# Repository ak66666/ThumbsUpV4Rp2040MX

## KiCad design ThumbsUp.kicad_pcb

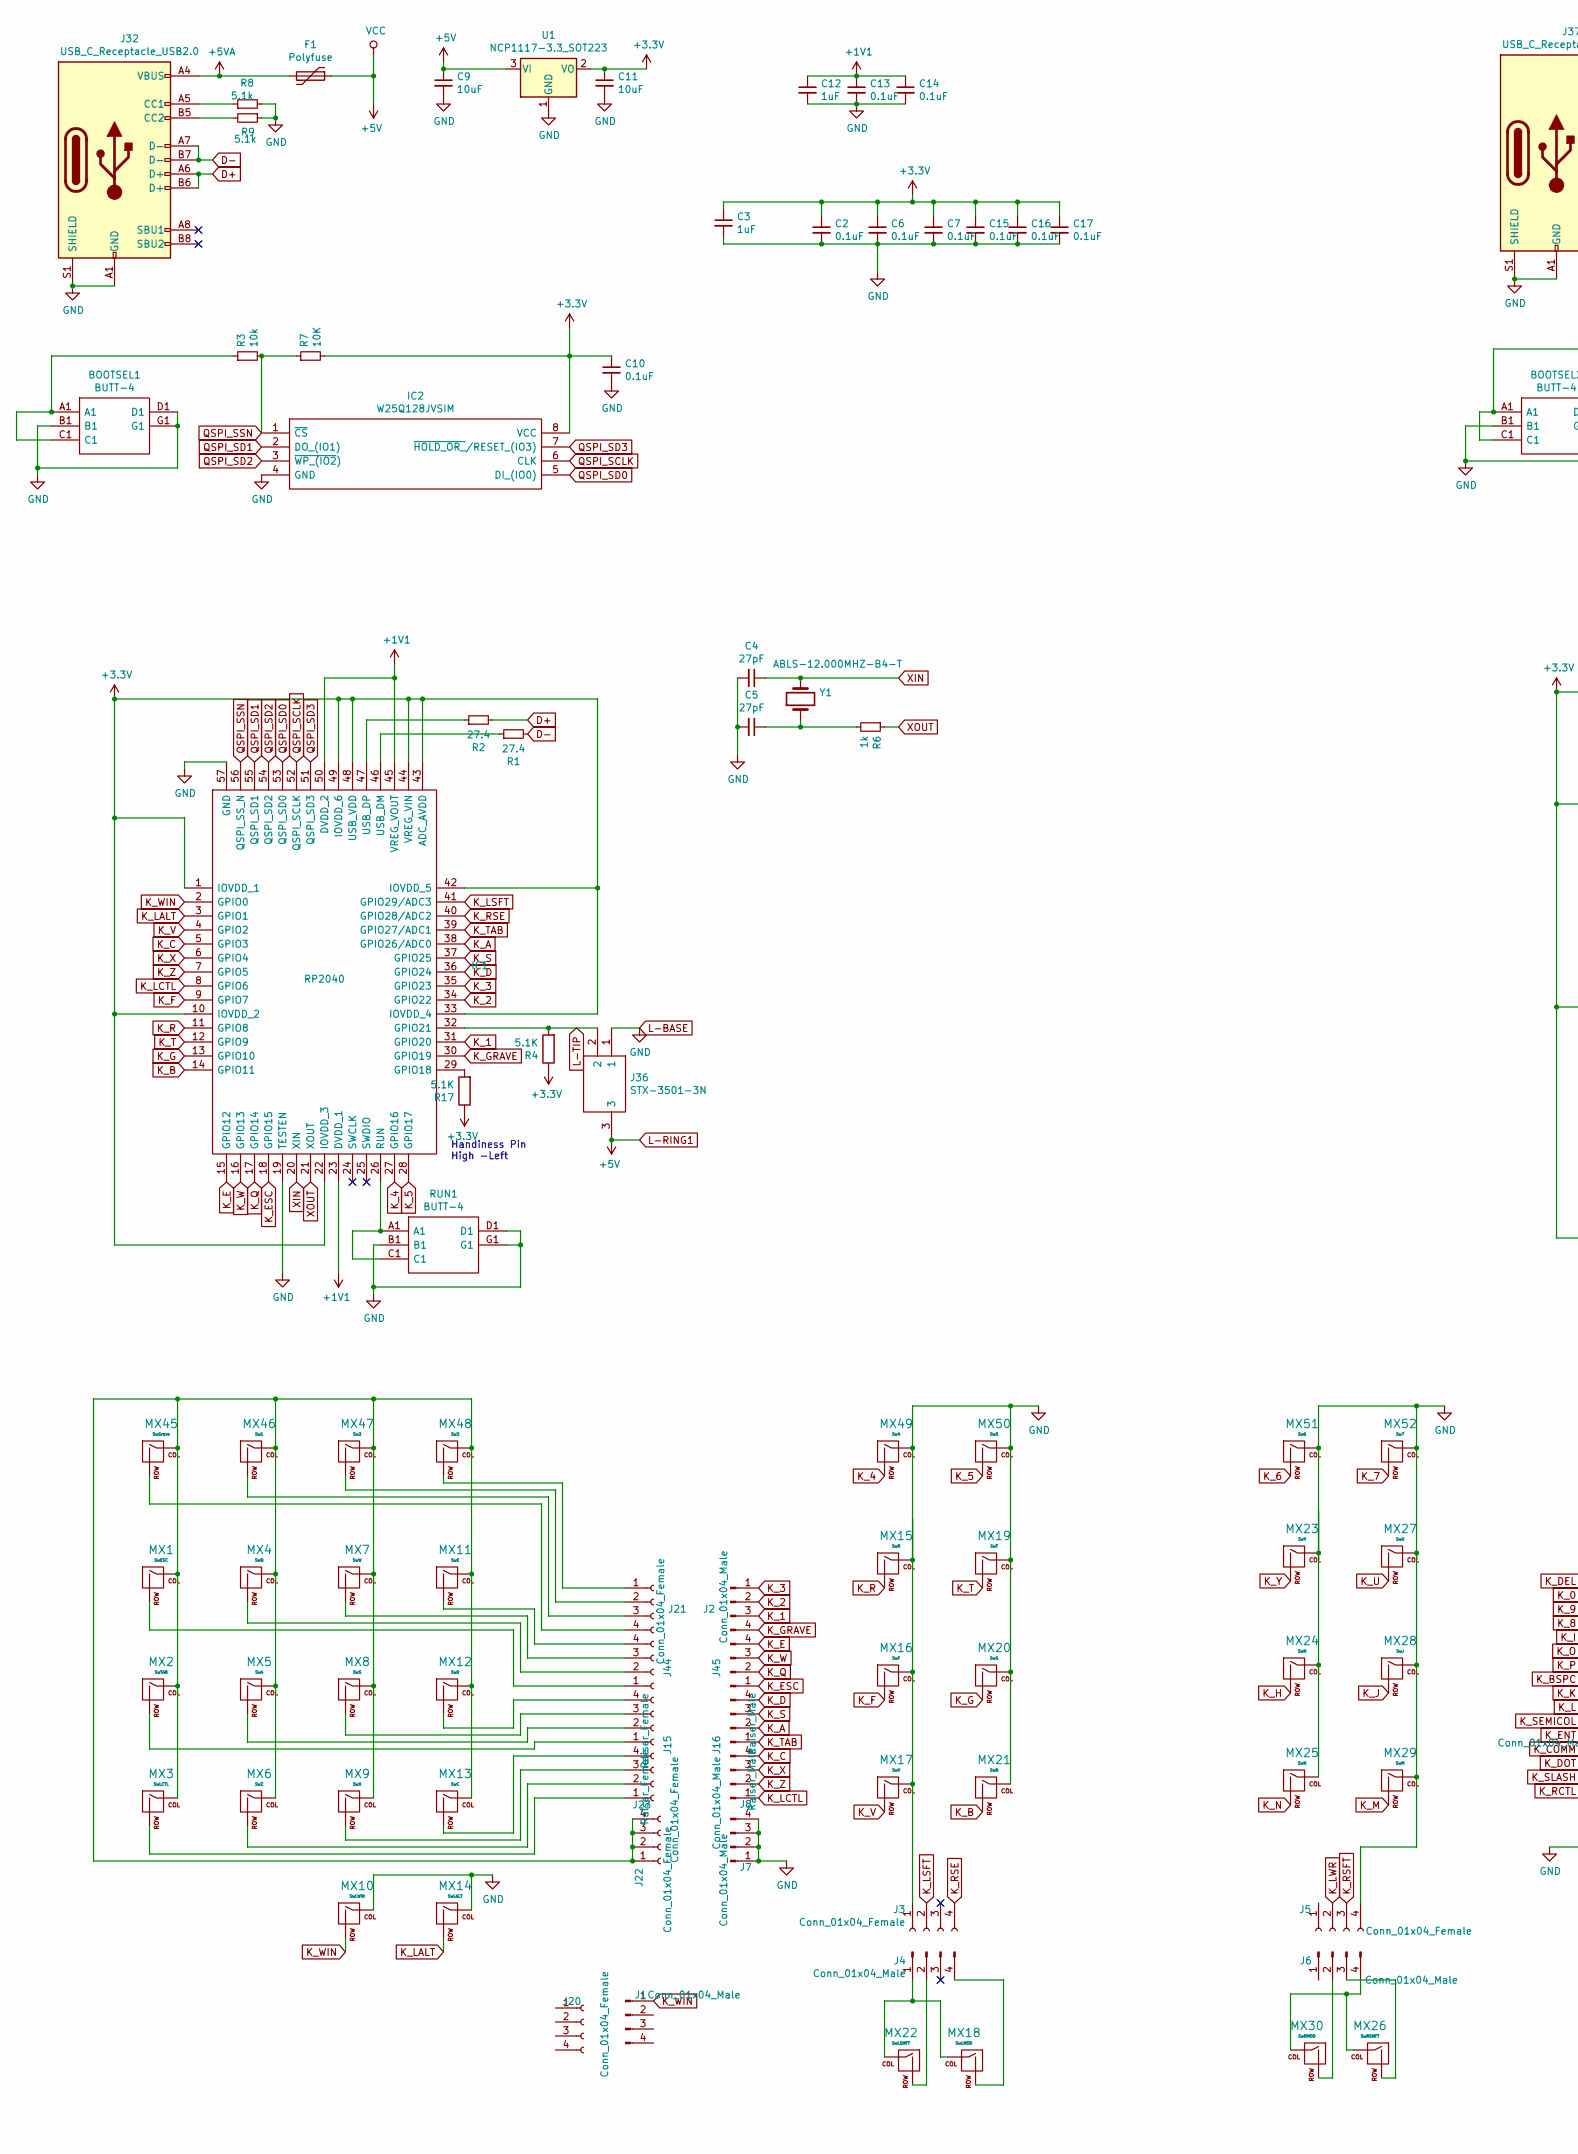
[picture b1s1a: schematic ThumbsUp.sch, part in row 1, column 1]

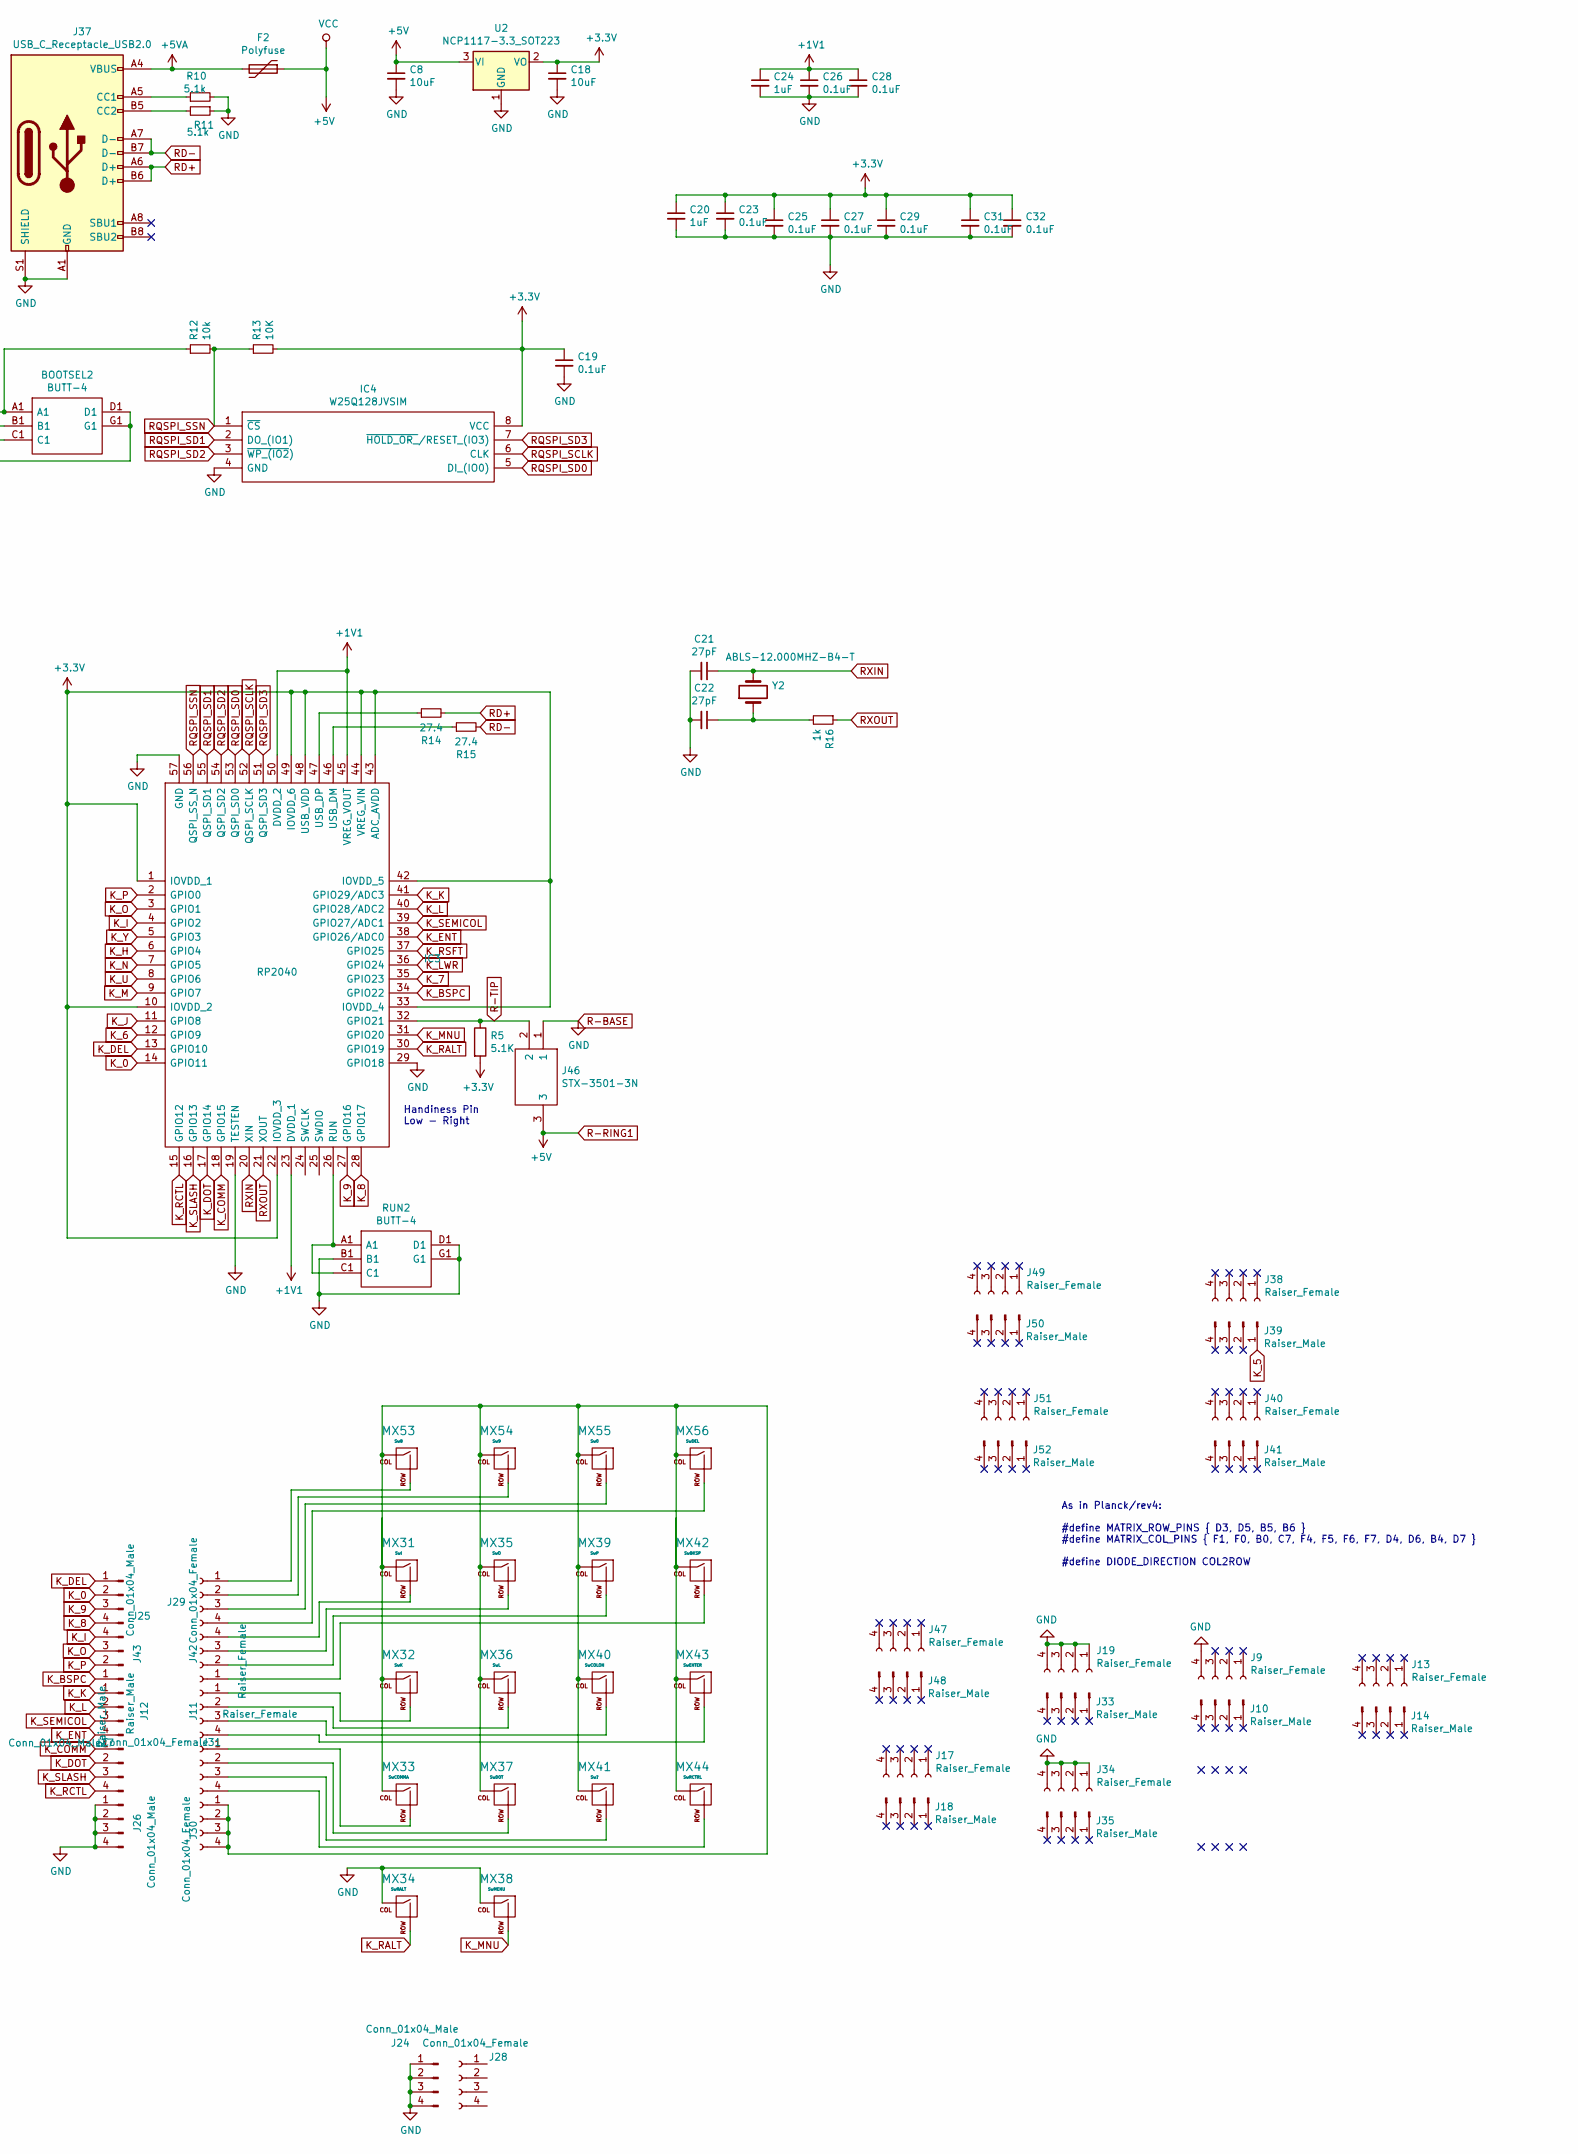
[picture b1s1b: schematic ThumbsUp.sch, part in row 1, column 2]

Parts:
BOOTSEL1, BOOTSEL2: BUTT-4; BUTT4; Manufacturer_Part_Number BUTT-4; Mouser Part Number 992-BUTT-4
C2, C6, C7, C10, C13, C14, C15, C16, C17, C19, C23, C25, C26, C27, C28, C29, C31, C32: 0.1uF; C_0402_1005Metric
C3, C12, C20, C24: 1uF; C_0402_1005Metric
C4, C5, C21, C22: 27pF; C_0402_1005Metric
C8, C9, C11, C18: 10uF; C_0402_1005Metric
F1, F2: Polyfuse; Fuse_1206_3216Metric
IC1, IC3: RP2040; QFN40P700X700X90-57N-D; Manufacturer_Part_Number RP2040
IC2, IC4: W25Q128JVSIM; SOIC127P790X216-8N; Manufacturer_Part_Number W25Q128JVSIM; Mouser Part Number 454-W25Q128JVSIM
J1, J2, J4, J6, J7, J8, J24, J25, J26, J27: Conn_01x04_Male; PinHeader_1x04_P2.54mm_Vertical
J3, J5, J20, J21, J22, J23, J28, J29, J30, J31: Conn_01x04_Female; PinSocket_1x04_P2.54mm_Vertical
J9, J11, J13, J15, J17, J19, J34, J38, J40, J42, J44, J47, J49, J51: Raiser_Female; PinSocket_1x04_P2.54mm_Vertical
J10, J12, J14, J16, J18, J33, J35, J39, J41, J43, J45, J48, J50, J52: Raiser_Male; PinHeader_1x04_P2.54mm_Vertical
J32, J37: USB_C_Receptacle_USB2.0; USB_C_Receptacle_Palconn_UTC16-G
J36, J46: STX-3501-3N; STX35013N; Manufacturer_Part_Number STX-3501-3N; Mouser Part Number 806-STX-3501-3N
MX1: SwESC; MX-1U-NoLED_HotSwap
MX2: SwTAB; MX-1U-NoLED_HotSwap
MX3: SwLCTL; MX-1U-NoLED_HotSwap
MX4: SwQ; MX-1U-NoLED_HotSwap
MX5: SwA; MX-1U-NoLED_HotSwap
MX6: SwZ; MX-1U-NoLED_HotSwap
MX7: SwW; MX-1U-NoLED_HotSwap
MX8: SwS; MX-1U-NoLED_HotSwap
MX9: SwX; MX-1U-NoLED_HotSwap
MX10: SwLWIN; MX-1U-NoLED_HotSwap
MX11: SwE; MX-1U-NoLED_HotSwap
MX12: SwD; MX-1U-NoLED_HotSwap
MX13: SwC; MX-1U-NoLED_HotSwap
MX14: SwLALT; MX-1U-NoLED_HotSwap
MX15: SwR; MX-1U-NoLED_HotSwap
MX16: SwF; MX-1U-NoLED_HotSwap
MX17: SwV; MX-1U-NoLED_HotSwap
MX18: SwLMOD; MX-1U-NoLED_HotSwap
MX19: SwT; MX-1U-NoLED_HotSwap
MX20: SwG; MX-1U-NoLED_HotSwap
MX21: SwB; MX-1U-NoLED_HotSwap
MX22: SwLSHFT; MX-1U-NoLED_HotSwap
MX23: SwY; MX-1U-NoLED_HotSwap
MX24: SwH; MX-1U-NoLED_HotSwap
MX25: SwN; MX-1U-NoLED_HotSwap
MX26: SwRSHFT; MX-1U-NoLED_HotSwap
MX27: SwU; MX-1U-NoLED_HotSwap
MX28: SwJ; MX-1U-NoLED_HotSwap
MX29: SwM; MX-1U-NoLED_HotSwap
MX30: SwRMOD; MX-1U-NoLED_HotSwap
MX31: SwI; MX-1U-NoLED_HotSwap
MX32: SwK; MX-1U-NoLED_HotSwap
MX33: SwCOMMA; MX-1U-NoLED_HotSwap
MX34: SwRALT; MX-1U-NoLED_HotSwap
MX35: SwO; MX-1U-NoLED_HotSwap
MX36: SwL; MX-1U-NoLED_HotSwap
MX37: SwDOT; MX-1U-NoLED_HotSwap
MX38: SwMENU; MX-1U-NoLED_HotSwap
MX39: SwP; MX-1U-NoLED_HotSwap
MX40: SwCOLON; MX-1U-NoLED_HotSwap
MX41: Sw?; MX-1U-NoLED_HotSwap
MX42: SwBKSP; MX-1U-NoLED_HotSwap
MX43: SwENTER; MX-1U-NoLED_HotSwap
MX44: SwRCTRL; MX-1U-NoLED_HotSwap
MX45: SwGrave; MX-1U-NoLED_HotSwap
MX46: Sw1; MX-1U-NoLED_HotSwap
MX47: Sw2; MX-1U-NoLED_HotSwap
MX48: Sw3; MX-1U-NoLED_HotSwap
MX49: Sw4; MX-1U-NoLED_HotSwap
MX50: Sw5; MX-1U-NoLED_HotSwap
MX51: Sw6; MX-1U-NoLED_HotSwap
MX52: Sw7; MX-1U-NoLED_HotSwap
MX53: Sw8; MX-1U-NoLED_HotSwap
MX54: Sw9; MX-1U-NoLED_HotSwap
MX55: Sw0; MX-1U-NoLED_HotSwap
MX56: SwDEL; MX-1U-NoLED_HotSwap
R1, R2, R14, R15: 27.4; R_0402_1005Metric
R3, R12: 10k; R_0402_1005Metric
R4, R5, R17: 5.1K; R_0402_1005Metric
R6, R16: 1k; R_0402_1005Metric
R7, R13: 10K; R_0402_1005Metric
R8, R9, R10, R11: 5.1k; R_0402_1005Metric
RUN1, RUN2: BUTT-4; BUTT4; Manufacturer_Part_Number BUTT-4; Mouser Part Number 992-BUTT-4
U1, U2: NCP1117-3.3_SOT223; SOT-223-3_TabPin2
Y1, Y2: ABLS-12.000MHZ-B4-T; HC%2f49US-(AT49)_1

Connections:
+1V1: C12.1, C13.1, C14.1, C24.1, C26.1, C28.1, IC1.23 (DVDD_1), IC1.45 (VREG_VOUT), IC1.50 (DVDD_2), IC3.23 (DVDD_1), IC3.45 (VREG_VOUT), IC3.50 (DVDD_2)
+3V3: C2.1, C3.1, C6.1, C7.1, C10.1, C11.1, C15.1, C16.1, C17.1, C18.1, C19.1, C20.1, C23.1, C25.1, C27.1, C29.1, C31.1, C32.1, IC1.1 (IOVDD_1), IC1.10 (IOVDD_2), IC1.22 (IOVDD_3), IC1.33 (IOVDD_4), IC1.42 (IOVDD_5), IC1.43 (ADC_AVDD), IC1.44 (VREG_VIN), IC1.48 (USB_VDD), IC1.49 (IOVDD_6), IC2.8 (VCC), IC3.1 (IOVDD_1), IC3.10 (IOVDD_2), IC3.22 (IOVDD_3), IC3.33 (IOVDD_4), IC3.42 (IOVDD_5), IC3.43 (ADC_AVDD), IC3.44 (VREG_VIN), IC3.48 (USB_VDD), IC3.49 (IOVDD_6), IC4.8 (VCC), R4.1, R5.2, R7.2, R13.2, R17.1, U1.2 (VO), U2.2 (VO)
+5VA: F1.2, F2.2, J32.A4 (VBUS), J32.A9 (VBUS), J32.B4 (VBUS), J32.B9 (VBUS), J37.A4 (VBUS), J37.A9 (VBUS), J37.B4 (VBUS), J37.B9 (VBUS)
D+: J32.A6 (D+), J32.B6 (D+), R2.2
D-: J32.A7 (D-), J32.B7 (D-), R1.2
K_0: IC3.14 (GPIO11), J25.2
K_1: IC1.31 (GPIO20), J2.3
K_2: IC1.34 (GPIO22), J2.2
K_3: IC1.35 (GPIO23), J2.1
K_4: IC1.27 (GPIO16), MX49.2 (ROW)
K_5: IC1.28 (GPIO17), J39.1, MX50.2 (ROW)
K_6: IC3.12 (GPIO9), MX51.2 (ROW)
K_7: IC3.35 (GPIO23), MX52.2 (ROW)
K_8: IC3.28 (GPIO17), J25.4
K_9: IC3.27 (GPIO16), J25.3
K_A: IC1.38 (GPIO26/ADC0), J16.2
K_B: IC1.14 (GPIO11), MX21.2 (ROW)
K_BSPC: IC3.34 (GPIO22), J43.1
K_C: IC1.5 (GPIO3), J8.4
K_COMM: IC3.18 (GPIO15), J27.1
K_D: IC1.36 (GPIO24), J16.4
K_DEL: IC3.13 (GPIO10), J25.1
K_DOT: IC3.17 (GPIO14), J27.2
K_E: IC1.15 (GPIO12), J45.4
K_ENT: IC3.38 (GPIO26/ADC0), J12.4
K_ESC: IC1.18 (GPIO15), J45.1
K_F: IC1.9 (GPIO7), MX16.2 (ROW)
K_G: IC1.13 (GPIO10), MX20.2 (ROW)
K_GRAVE: IC1.30 (GPIO19), J2.4
K_H: IC3.6 (GPIO4), MX24.2 (ROW)
K_I: IC3.4 (GPIO2), J43.4
K_J: IC3.11 (GPIO8), MX28.2 (ROW)
K_K: IC3.41 (GPIO29/ADC3), J12.1
K_L: IC3.40 (GPIO28/ADC2), J12.2
K_LALT: IC1.3 (GPIO1), MX14.2 (ROW)
K_LCTL: IC1.8 (GPIO6), J8.1
K_LSFT: IC1.41 (GPIO29/ADC3), J3.2
K_LWR: IC3.36 (GPIO24), J5.2
K_M: IC3.9 (GPIO7), MX29.2 (ROW)
K_MNU: IC3.31 (GPIO20), MX38.2 (ROW)
K_N: IC3.7 (GPIO5), MX25.2 (ROW)
K_O: IC3.3 (GPIO1), J43.3
K_P: IC3.2 (GPIO0), J43.2
K_Q: IC1.17 (GPIO14), J45.2
K_R: IC1.11 (GPIO8), MX15.2 (ROW)
K_RALT: IC3.30 (GPIO19), MX34.2 (ROW)
K_RCTL: IC3.15 (GPIO12), J27.4
K_RSE: IC1.40 (GPIO28/ADC2), J3.4
K_RSFT: IC3.37 (GPIO25), J5.3
K_S: IC1.37 (GPIO25), J16.3
K_SEMICOL: IC3.39 (GPIO27/ADC1), J12.3
K_SLASH: IC3.16 (GPIO13), J27.3
K_T: IC1.12 (GPIO9), MX19.2 (ROW)
K_TAB: IC1.39 (GPIO27/ADC1), J16.1
K_U: IC3.8 (GPIO6), MX27.2 (ROW)
K_V: IC1.4 (GPIO2), MX17.2 (ROW)
K_W: IC1.16 (GPIO13), J45.3
K_WIN: IC1.2 (GPIO0), J1.1, MX10.2 (ROW)
K_X: IC1.6 (GPIO4), J8.3
K_Y: IC3.5 (GPIO3), MX23.2 (ROW)
K_Z: IC1.7 (GPIO5), J8.2
L-BASE: BOOTSEL1.B1, BOOTSEL1.D1, BOOTSEL1.G1, BOOTSEL2.B1, BOOTSEL2.D1, BOOTSEL2.G1, C2.2, C3.2, C4.2, C5.2, C6.2, C7.2, C8.2, C9.2, C10.2, C11.2, C12.2, C13.2, C14.2, C15.2, C16.2, C17.2, C18.2, C19.2, C20.2, C21.2, C22.2, C23.2, C24.2, C25.2, C26.2, C27.2, C28.2, C29.2, C31.2, C32.2, IC1.19 (TESTEN), IC1.57 (GND), IC2.4 (GND), IC3.19 (TESTEN), IC3.29 (GPIO18), IC3.57 (GND), IC4.4 (GND), J3.1, J5.4, J7.1, J7.2, J7.3, J7.4, J9.4, J19.1, J19.2, J19.3, J19.4, J24.1, J24.2, J24.3, J24.4, J26.1, J26.2, J26.3, J26.4, J32.A1 (GND), J32.A12 (GND), J32.B1 (GND), J32.B12 (GND), J32.S1 (SHIELD), J34.1, J34.2, J34.3, J34.4, J36.1, J37.A1 (GND), J37.A12 (GND), J37.B1 (GND), J37.B12 (GND), J37.S1 (SHIELD), J46.1, MX10.1 (COL), MX14.1 (COL), MX15.1 (COL), MX16.1 (COL), MX17.1 (COL), MX19.1 (COL), MX20.1 (COL), MX21.1 (COL), MX23.1 (COL), MX24.1 (COL), MX25.1 (COL), MX27.1 (COL), MX28.1 (COL), MX29.1 (COL), MX34.1 (COL), MX38.1 (COL), MX49.1 (COL), MX50.1 (COL), MX51.1 (COL), MX52.1 (COL), R8.2, R9.1, R10.2, R11.1, RUN1.B1, RUN1.D1, RUN1.G1, RUN2.B1, RUN2.D1, RUN2.G1, U1.1 (GND), U2.1 (GND)
L-RING1: C8.1, C9.1, F1.1, F2.1, J36.3, J46.3, U1.3 (VI), U2.3 (VI)
L-TIP: IC1.32 (GPIO21), J36.2, R4.2
unnamed: BOOTSEL1.A1, BOOTSEL1.C1, R3.1
unnamed: BOOTSEL2.A1, BOOTSEL2.C1, R12.1
unnamed: C5.1, R6.2, Y1.1
unnamed: C22.1, R16.2, Y2.1
unnamed: IC1.26 (RUN), RUN1.A1, RUN1.C1
unnamed: IC1.29 (GPIO18), R17.2
unnamed: IC1.46 (USB_DM), R1.1
unnamed: IC1.47 (USB_DP), R2.1
unnamed: IC3.26 (RUN), RUN2.A1, RUN2.C1
unnamed: IC3.46 (USB_DM), R15.1
unnamed: IC3.47 (USB_DP), R14.1
unnamed: J4.1, MX18.1 (COL), MX22.1 (COL)
unnamed: J4.2, MX22.2 (ROW)
unnamed: J4.4, MX18.2 (ROW)
unnamed: J6.2, MX30.2 (ROW)
unnamed: J6.3, MX26.2 (ROW)
unnamed: J6.4, MX26.1 (COL), MX30.1 (COL)
unnamed: J11.1, MX32.2 (ROW)
unnamed: J11.2, MX36.2 (ROW)
unnamed: J11.3, MX40.2 (ROW)
unnamed: J11.4, MX43.2 (ROW)
unnamed: J15.1, MX2.2 (ROW)
unnamed: J15.2, MX5.2 (ROW)
unnamed: J15.3, MX8.2 (ROW)
unnamed: J15.4, MX12.2 (ROW)
unnamed: J21.1, MX48.2 (ROW)
unnamed: J21.2, MX47.2 (ROW)
unnamed: J21.3, MX46.2 (ROW)
unnamed: J21.4, MX45.2 (ROW)
unnamed: J22.1, J22.2, J22.3, J22.4, MX1.1 (COL), MX2.1 (COL), MX3.1 (COL), MX4.1 (COL), MX5.1 (COL), MX6.1 (COL), MX7.1 (COL), MX8.1 (COL), MX9.1 (COL), MX11.1 (COL), MX12.1 (COL), MX13.1 (COL), MX45.1 (COL), MX46.1 (COL), MX47.1 (COL), MX48.1 (COL)
unnamed: J23.1, MX3.2 (ROW)
unnamed: J23.2, MX6.2 (ROW)
unnamed: J23.3, MX9.2 (ROW)
unnamed: J23.4, MX13.2 (ROW)
unnamed: J29.1, MX53.2 (ROW)
unnamed: J29.2, MX54.2 (ROW)
unnamed: J29.3, MX55.2 (ROW)
unnamed: J29.4, MX56.2 (ROW)
unnamed: J30.1, J30.2, J30.3, J30.4, MX31.1 (COL), MX32.1 (COL), MX33.1 (COL), MX35.1 (COL), MX36.1 (COL), MX37.1 (COL), MX39.1 (COL), MX40.1 (COL), MX41.1 (COL), MX42.1 (COL), MX43.1 (COL), MX44.1 (COL), MX53.1 (COL), MX54.1 (COL), MX55.1 (COL), MX56.1 (COL)
unnamed: J31.1, MX33.2 (ROW)
unnamed: J31.2, MX37.2 (ROW)
unnamed: J31.3, MX41.2 (ROW)
unnamed: J31.4, MX44.2 (ROW)
unnamed: J32.A5 (CC1), R8.1
unnamed: J32.B5 (CC2), R9.2
unnamed: J37.A5 (CC1), R10.1
unnamed: J37.B5 (CC2), R11.2
unnamed: J42.1, MX42.2 (ROW)
unnamed: J42.2, MX39.2 (ROW)
unnamed: J42.3, MX35.2 (ROW)
unnamed: J42.4, MX31.2 (ROW)
unnamed: J44.1, MX1.2 (ROW)
unnamed: J44.2, MX4.2 (ROW)
unnamed: J44.3, MX7.2 (ROW)
unnamed: J44.4, MX11.2 (ROW)
QSPI_SCLK: IC1.52 (QSPI_SCLK), IC2.6 (CLK)
QSPI_SD0: IC1.53 (QSPI_SD0), IC2.5 (DI_(IO0))
QSPI_SD1: IC1.55 (QSPI_SD1), IC2.2 (DO_(IO1))
QSPI_SD2: IC1.54 (QSPI_SD2), IC2.3 (~WP_(IO2))
QSPI_SD3: IC1.51 (QSPI_SD3), IC2.7 (~HOLD_OR_~/RESET_(IO3))
QSPI_SSN: IC1.56 (QSPI_SS_N), IC2.1 (~CS), R3.2, R7.1
R-TIP: IC3.32 (GPIO21), J46.2, R5.1
RD+: J37.A6 (D+), J37.B6 (D+), R14.2
RD-: J37.A7 (D-), J37.B7 (D-), R15.2
RQSPI_SCLK: IC3.52 (QSPI_SCLK), IC4.6 (CLK)
RQSPI_SD0: IC3.53 (QSPI_SD0), IC4.5 (DI_(IO0))
RQSPI_SD1: IC3.55 (QSPI_SD1), IC4.2 (DO_(IO1))
RQSPI_SD2: IC3.54 (QSPI_SD2), IC4.3 (~WP_(IO2))
RQSPI_SD3: IC3.51 (QSPI_SD3), IC4.7 (~HOLD_OR_~/RESET_(IO3))
RQSPI_SSN: IC3.56 (QSPI_SS_N), IC4.1 (~CS), R12.2, R13.1
RXIN: C21.1, IC3.20 (XIN), Y2.2
RXOUT: IC3.21 (XOUT), R16.1
XIN: C4.1, IC1.20 (XIN), Y1.2
XOUT: IC1.21 (XOUT), R6.1

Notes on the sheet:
As in Planck/rev4: #define MATRIX_ROW_PINS { D3, D5, B5, B6 } #define MATRIX_COL_PINS { F1, F0, B0, C7, F4, F5, F6, F7, D4, D6, B4, D7 } #define DIODE_DIRECTION COL2ROW
Handiness Pin High -Left
Handiness Pin Low - Right

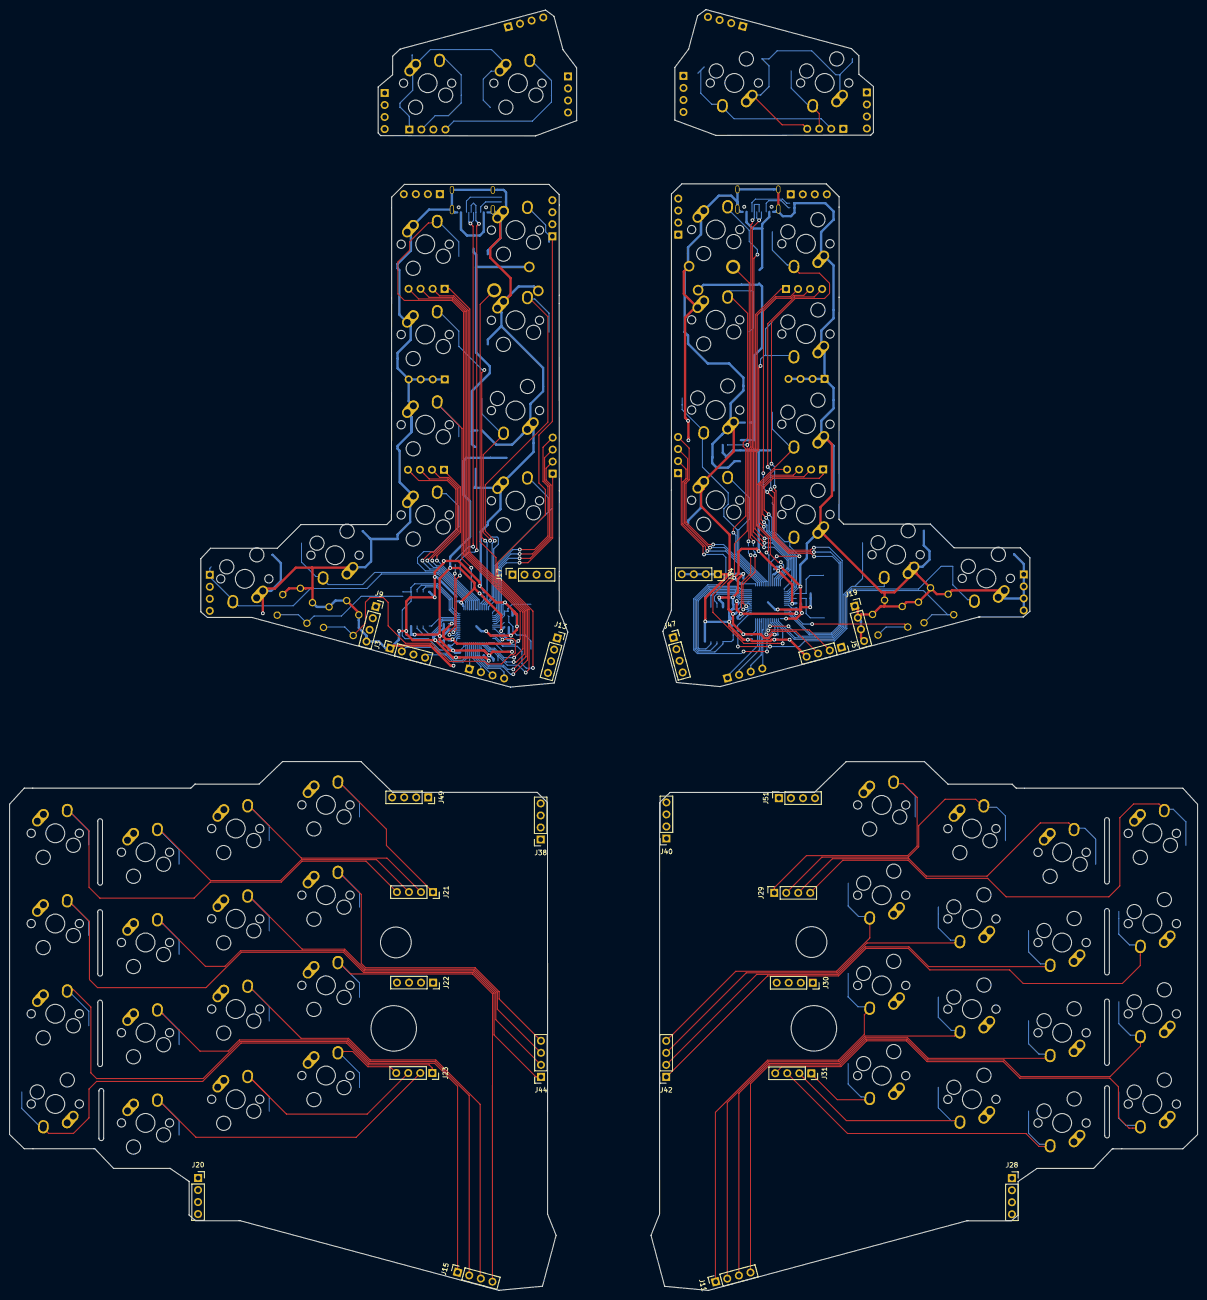
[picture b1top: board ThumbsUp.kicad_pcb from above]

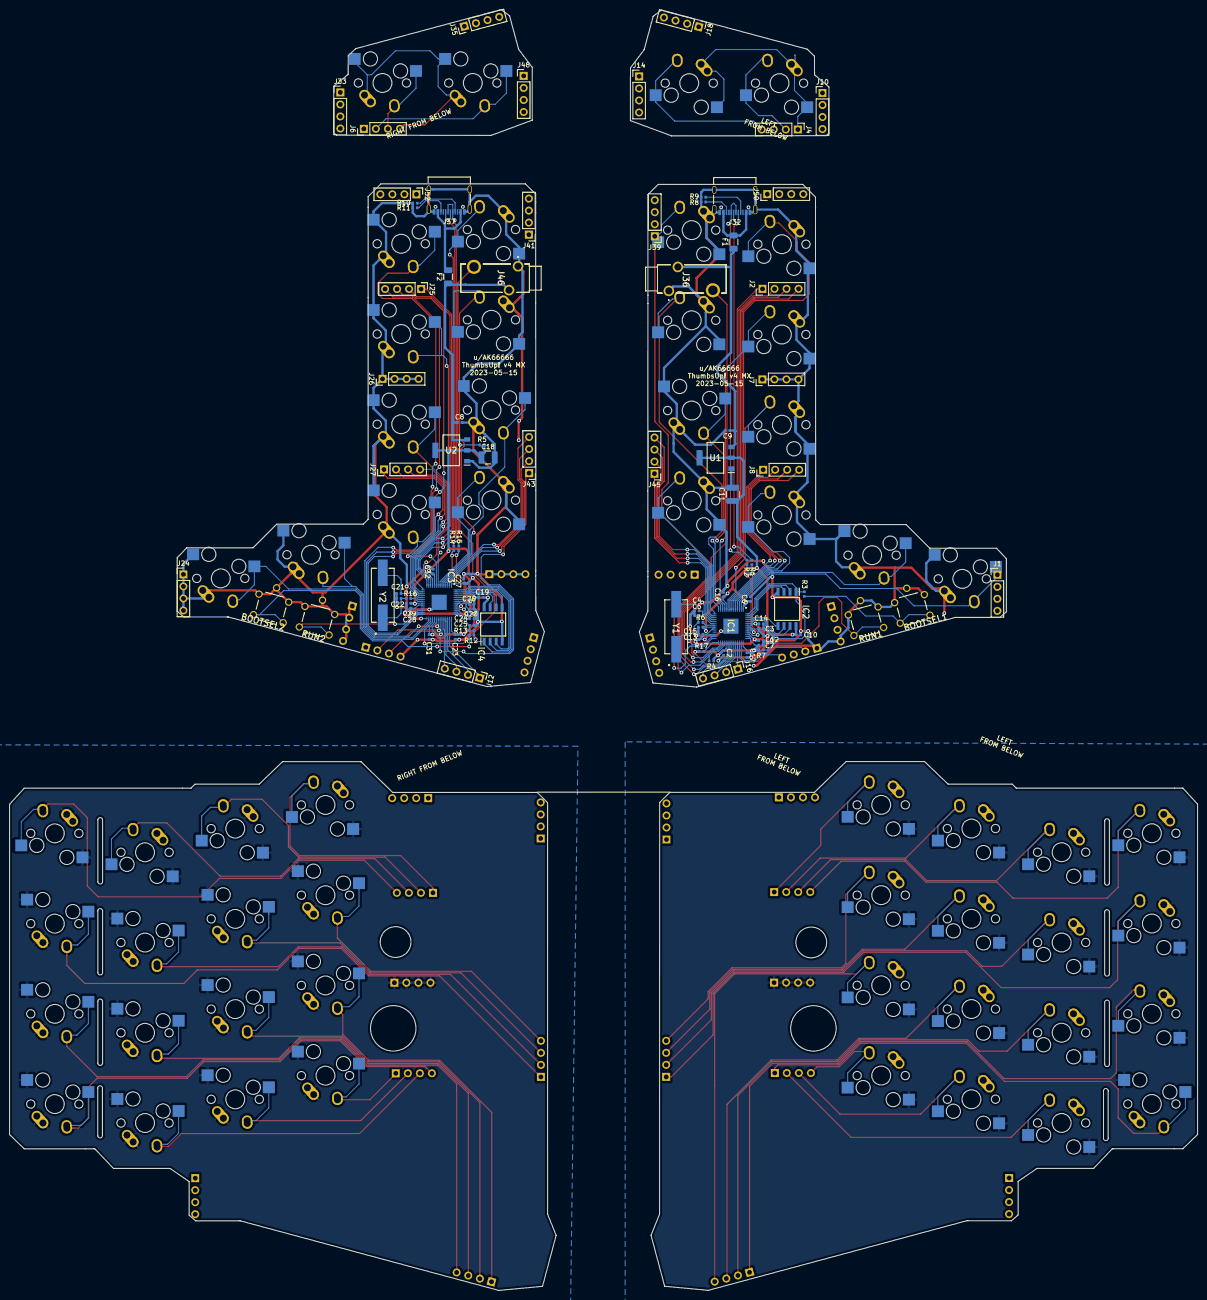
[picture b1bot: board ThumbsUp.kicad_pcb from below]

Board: 2 copper layers, 250.8 x 270.5 mm, 169 parts (89 on the bottom side), 138 nets.

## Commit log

2023-05-07 Created v4 for MX version
2023-05-07 Moved the tracks out of L-inner corners
2023-05-08 Redrew the lower PCB
2023-05-08 Reverted the schematics changres
2023-05-16 Adjusted outlines, replaced pushbuttons
2023-05-16 Moved buttons to back side, fixed disconnects
2023-05-16 Moved tracks farther from the edges.
2023-05-18 Populated DNF resistors with 10K.
2023-05-18 Put the screensilk back on
2023-05-19 Generated Gerbers
2023-05-19 Corrected BOMs
2023-06-07 Moved tracks of K_5 away from K_E, K4 from K_GRAVE to avoid short circuits in some of the board copies.
2023-06-08 Left L2 - straightened the USB signal lines.
2023-06-11 Removed fill zone from the middle layer - they were shortening the areas under MCU and USB connectors.
2023-06-12 Replacing voltage regulators with available parts - schematics updated.
2023-06-13 Replacing voltage regulators with available parts - PCBs updated.
2023-06-14 Added silkscreen before generating Gerbers.
2023-06-14 Re-Generated Gerbers for L2, R2. BOMs, POSes.
2023-06-14 . & git push
